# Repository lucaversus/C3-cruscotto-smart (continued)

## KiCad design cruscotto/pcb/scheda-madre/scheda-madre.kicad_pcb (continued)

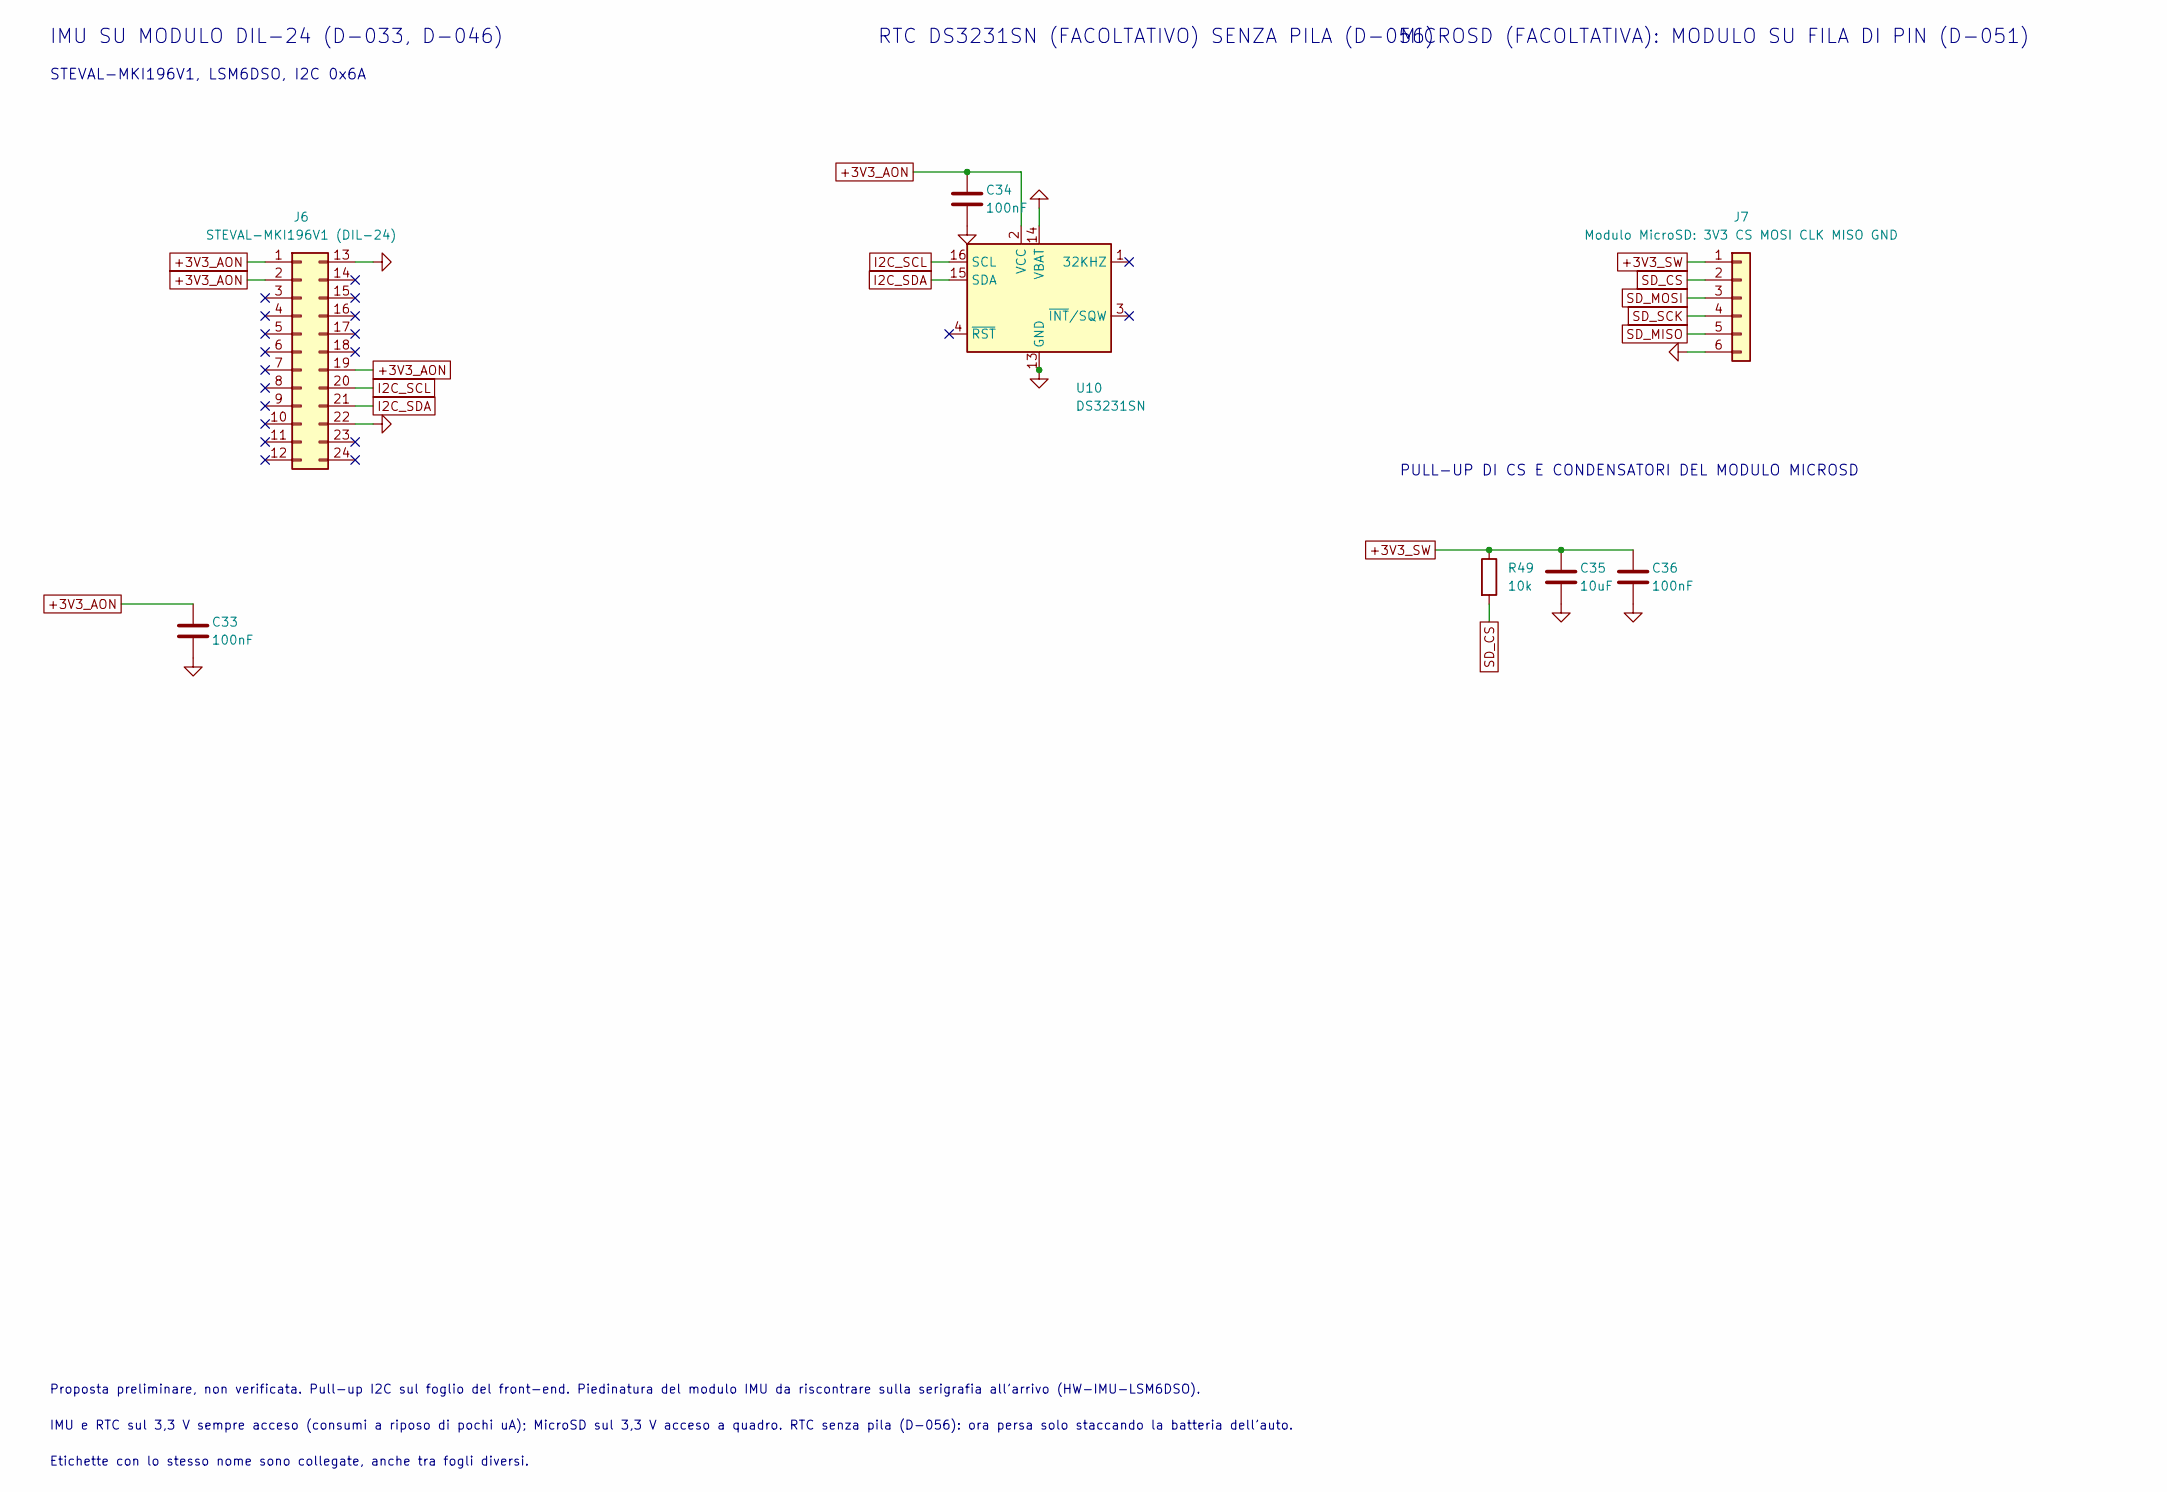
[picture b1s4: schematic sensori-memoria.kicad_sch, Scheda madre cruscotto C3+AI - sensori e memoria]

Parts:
C33, C34, C36: 100nF; C_0805_2012Metric_Pad1.18x1.45mm_HandSolder
C35: 10uF; C_1206_3216Metric_Pad1.33x1.80mm_HandSolder
J6: STEVAL-MKI196V1 (DIL-24); ST_DIL24_Adapter_W15.0mm
J7: Modulo MicroSD: 3V3 CS MOSI CLK MISO GND; PinHeader_1x06_P2.54mm_Vertical
R49: 10k; R_0805_2012Metric_Pad1.20x1.40mm_HandSolder
U10: DS3231SN; SOIC-16W_7.5x10.3mm_P1.27mm

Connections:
+3V3_AON: C33.1, C34.1, J6.1, J6.2, J6.19, U10.2 (VCC); also elsewhere on the board
+3V3_SW: C35.1, C36.1, J7.1, R49.1; also elsewhere on the board
GND: C33.2, C34.2, C35.2, C36.2, J6.13, J6.22, J7.6, U10.5 (GND), U10.6 (GND), U10.7 (GND), U10.8 (GND), U10.9 (GND), U10.10 (GND), U10.11 (GND), U10.12 (GND), U10.13 (GND), U10.14 (VBAT); also elsewhere on the board
I2C_SCL: J6.20, U10.16 (SCL); also elsewhere on the board
I2C_SDA: J6.21, U10.15 (SDA); also elsewhere on the board
SD_CS: J7.2, R49.2; also elsewhere on the board
SD_MISO: J7.5; also elsewhere on the board
SD_MOSI: J7.3; also elsewhere on the board
SD_SCK: J7.4; also elsewhere on the board

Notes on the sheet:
IMU SU MODULO DIL-24 (D-033, D-046)
STEVAL-MKI196V1, LSM6DSO, I2C 0x6A
RTC DS3231SN (FACOLTATIVO) SENZA PILA (D-056)
MICROSD (FACOLTATIVA): MODULO SU FILA DI PIN (D-051)
PULL-UP DI CS E CONDENSATORI DEL MODULO MICROSD
Proposta preliminare, non verificata. Pull-up I2C sul foglio del front-end. Piedinatura del modulo IMU da riscontrare sulla serigrafia all’arrivo (HW-IMU-LSM6DSO).
IMU e RTC sul 3,3 V sempre acceso (consumi a riposo di pochi uA); MicroSD sul 3,3 V acceso a quadro. RTC senza pila (D-056): ora persa solo staccando la batteria dell’auto.
Etichette con lo stesso nome sono collegate, anche tra fogli diversi.

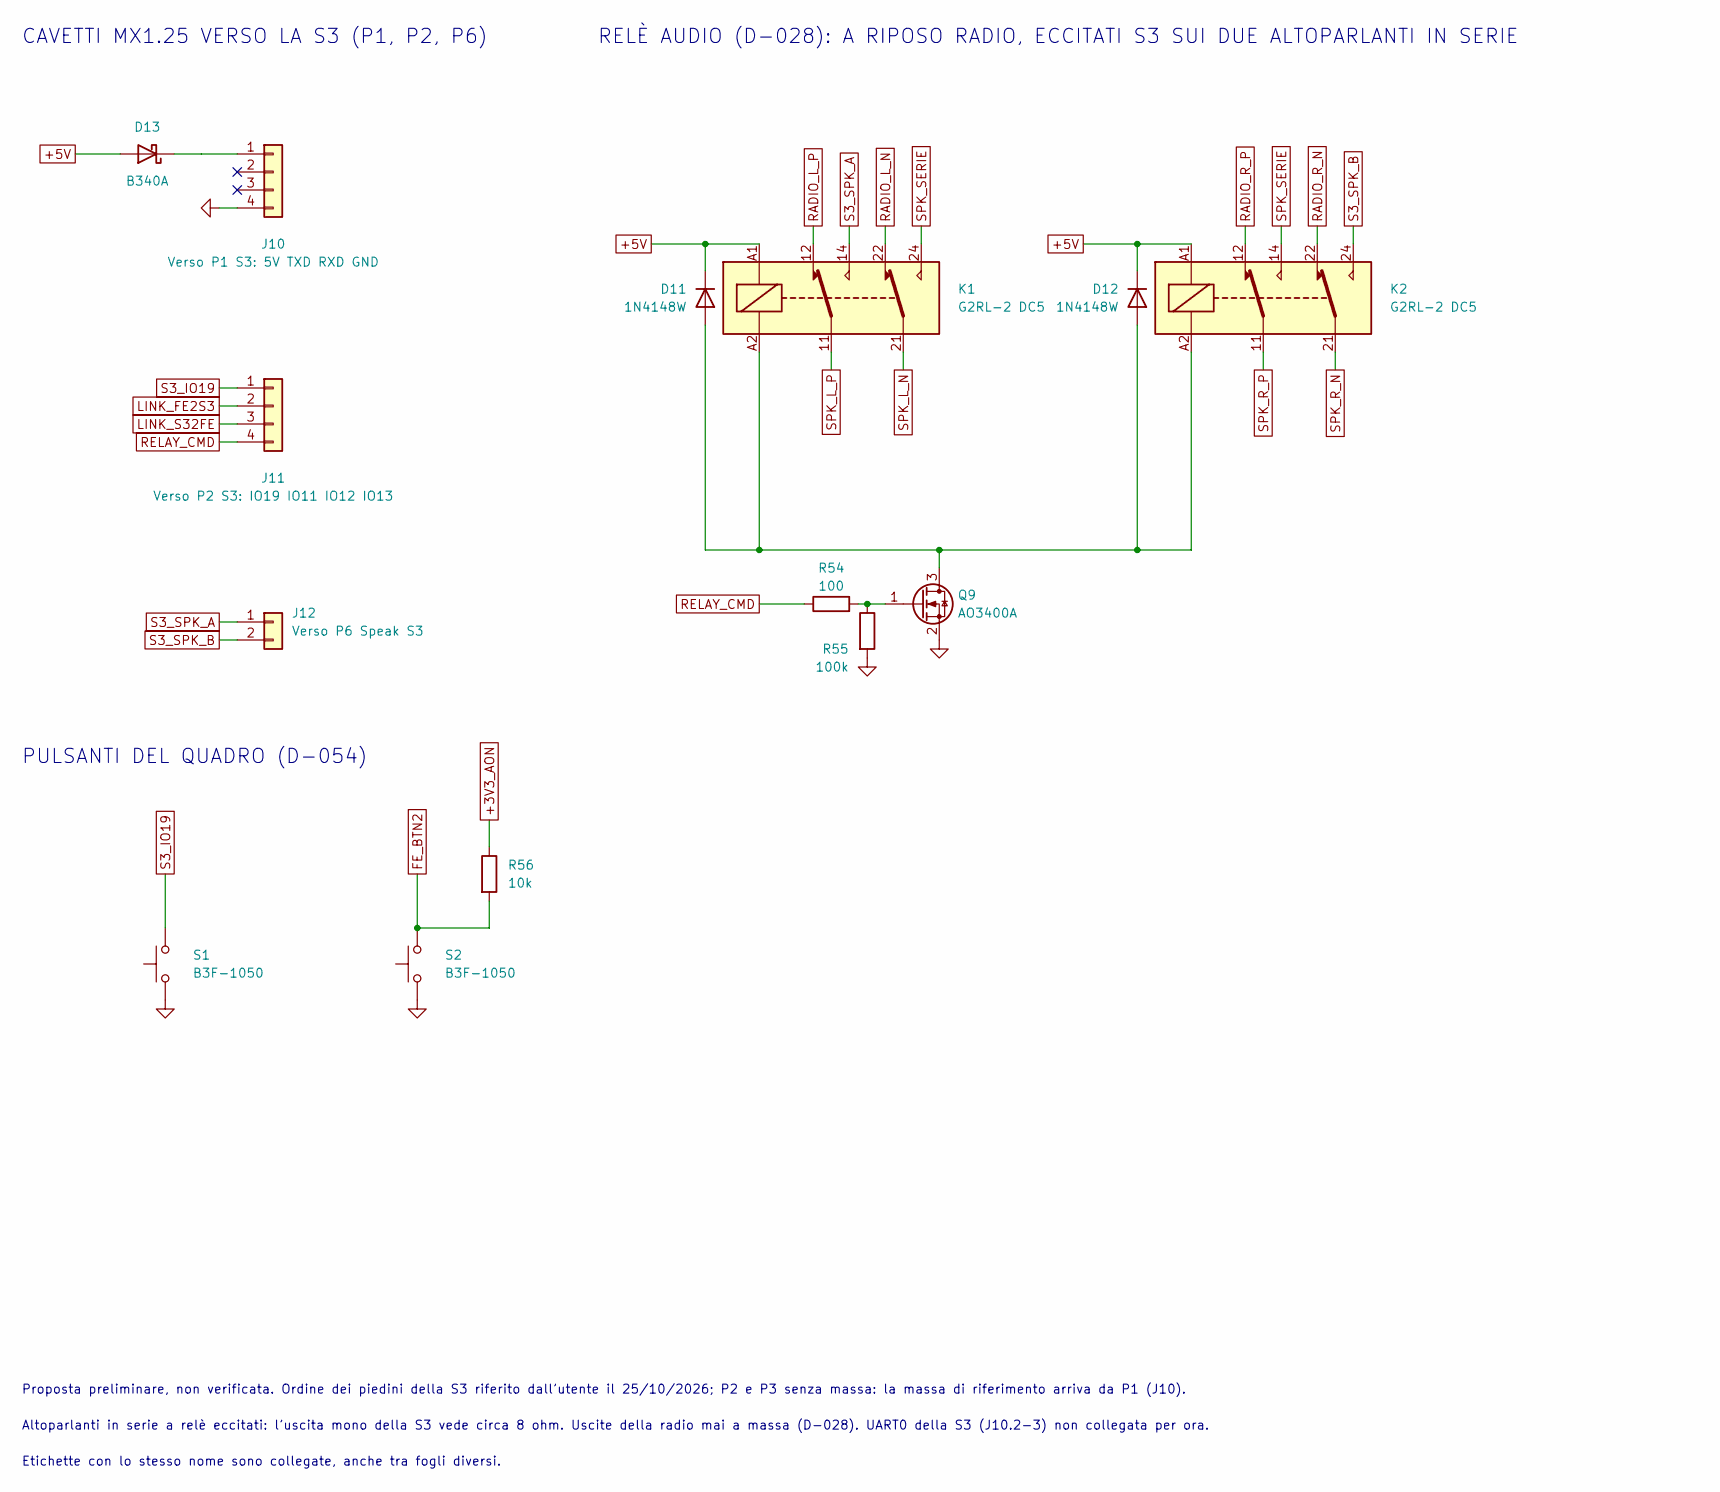
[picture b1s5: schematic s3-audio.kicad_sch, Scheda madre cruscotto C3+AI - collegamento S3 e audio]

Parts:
D11, D12: 1N4148W; D_SOD-123
D13: B340A; D_SMA
J10: Verso P1 S3: 5V TXD RXD GND; SolderWire-0.127sqmm_1x04_P3.7mm_D0.48mm_OD1mm
J11: Verso P2 S3: IO19 IO11 IO12 IO13; SolderWire-0.127sqmm_1x04_P3.7mm_D0.48mm_OD1mm
J12: Verso P6 Speak S3; SolderWire-0.127sqmm_1x02_P3.7mm_D0.48mm_OD1mm
K1, K2: G2RL-2 DC5; Relay_DPDT_Omron_G2RL-2
Q9: AO3400A; SOT-23
R54: 100; R_0805_2012Metric_Pad1.20x1.40mm_HandSolder
R55: 100k; R_0805_2012Metric_Pad1.20x1.40mm_HandSolder
R56: 10k; R_0805_2012Metric_Pad1.20x1.40mm_HandSolder
S1, S2: B3F-1050; SW_PUSH_6mm_H7.3mm

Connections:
+3V3_AON: R56.1; also elsewhere on the board
+5V: D11.1 (K), D12.1 (K), D13.2 (A), K1.A1, K2.A1; also elsewhere on the board
FE_BTN2: R56.2, S2.2; also elsewhere on the board
GND: J10.4, Q9.2 (S), R55.2, S1.1, S2.1; also elsewhere on the board
LINK_FE2S3: J11.2; also elsewhere on the board
LINK_S32FE: J11.3; also elsewhere on the board
unnamed: D11.2 (A), D12.2 (A), K1.A2, K2.A2, Q9.3 (D)
unnamed: D13.1 (K), J10.1
unnamed: Q9.1 (G), R54.2, R55.1
RADIO_L_N: K1.22; also elsewhere on the board
RADIO_L_P: K1.12; also elsewhere on the board
RADIO_R_N: K2.22; also elsewhere on the board
RADIO_R_P: K2.12; also elsewhere on the board
RELAY_CMD: J11.4, R54.1
S3_IO19: J11.1, S1.2
S3_SPK_A: J12.1, K1.14
S3_SPK_B: J12.2, K2.24
SPK_L_N: K1.21; also elsewhere on the board
SPK_L_P: K1.11; also elsewhere on the board
SPK_R_N: K2.21; also elsewhere on the board
SPK_R_P: K2.11; also elsewhere on the board
SPK_SERIE: K1.24, K2.14

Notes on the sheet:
PULSANTI DEL QUADRO (D-054)
CAVETTI MX1.25 VERSO LA S3 (P1, P2, P6)
RELÈ AUDIO (D-028): A RIPOSO RADIO, ECCITATI S3 SUI DUE ALTOPARLANTI IN SERIE
Proposta preliminare, non verificata. Ordine dei piedini della S3 riferito dall’utente il 25/10/2026; P2 e P3 senza massa: la massa di riferimento arriva da P1 (J10).
Altoparlanti in serie a relè eccitati: l’uscita mono della S3 vede circa 8 ohm. Uscite della radio mai a massa (D-028). UART0 della S3 (J10.2-3) non collegata per ora.
Etichette con lo stesso nome sono collegate, anche tra fogli diversi.

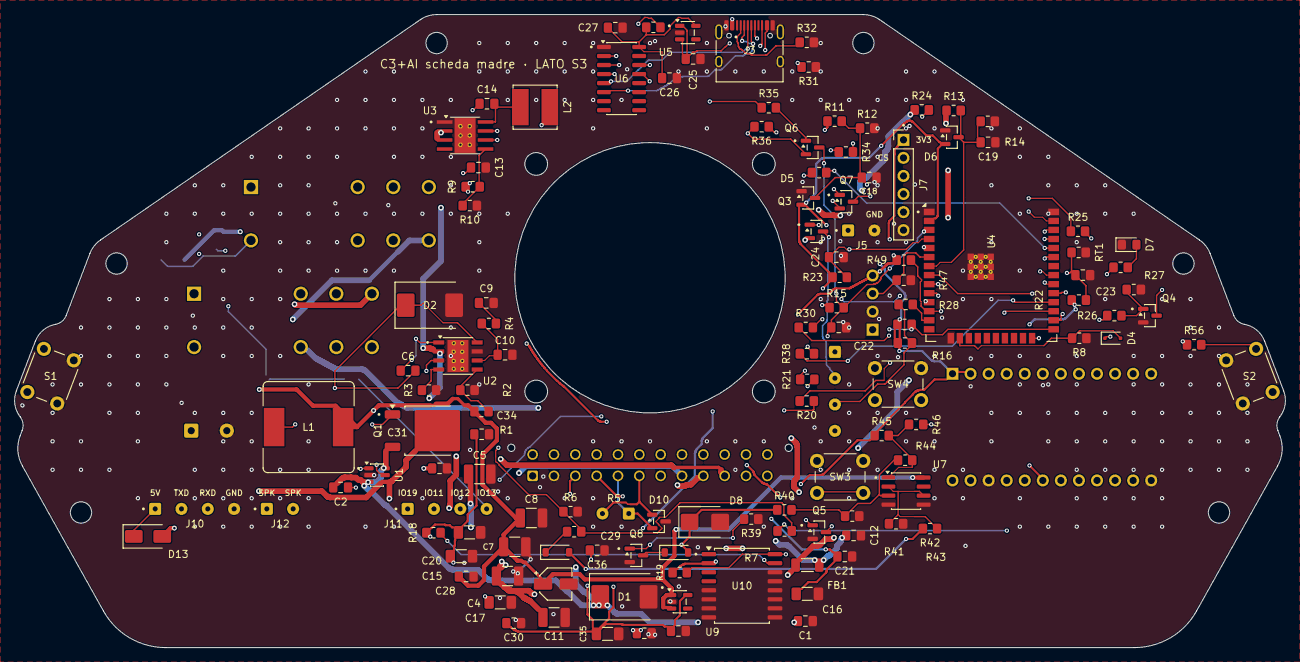
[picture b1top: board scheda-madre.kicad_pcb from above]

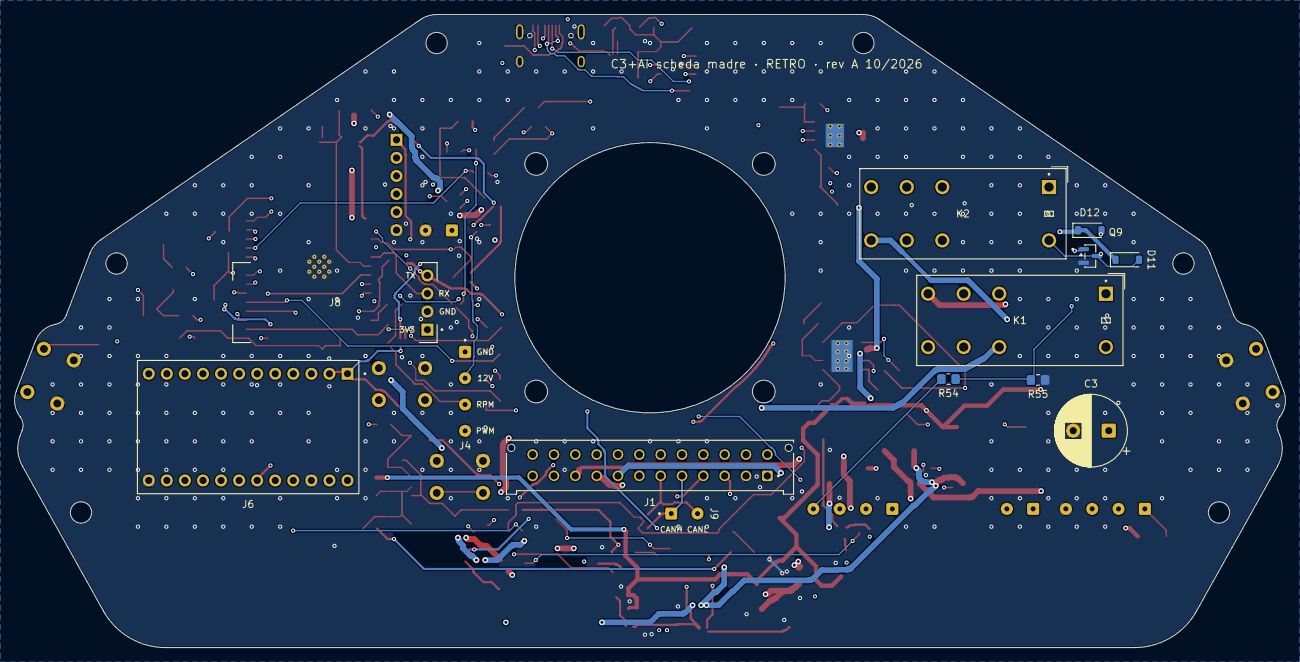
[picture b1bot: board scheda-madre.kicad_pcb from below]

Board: 4 copper layers, 178.7 x 89.0 mm, 149 parts (14 on the bottom side), 95 nets.

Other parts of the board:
H1, H2, H3, H4, H5, H6: Foro Ø3 (D-045); MountingHole_3mm
H7, H8, H9, H10: Ventola 40x40; MountingHole_3.2mm_M3
VENT1: Delta AFB0412VA-00

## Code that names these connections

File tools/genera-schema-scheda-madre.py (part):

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       note='Vie 16-24 riserva; assegnazione bozza (D-044)')
wire((30.48, 160.02), (30.48, 165.1))
flag('VBAT_IN', (30.48, 160.02))
label('VBAT_IN', (30.48, 165.1), 270)
flag('GND', (45.72, 160.02))
gnd((45.72, 160.02))

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wire((78.74, Y), 'D1.1', 'C1.1', (97.79, Y), (114.3, Y), 'Q1.3')
wire('Q1.2', (129.54, Y), (134.62, Y), 'C3.1', (149.86, Y), 'FB1.1')
wire('FB1.2', (165.1, Y), (170.18, Y))
label('VBAT_IN', (78.74, Y), 180)
wire((134.62, Y), (134.62, Y - 5.08))
label('VBAT_P', (134.62, Y - 5.08), 90)
flag('VBAT_P', (149.86, Y))
flag('+12V_F', (165.1, Y))
label('+12V_F', (170.18, Y), 0)
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wire('D3.1', 'R5.1')
wire('R5.2', (238.76, 88.9))
wire('D3.2', (209.55, 88.9))
label('KEY_IN', (209.55, 88.9), 180)
R('R7', '10k', 228.6, 101.6, 'HOLD_D', 'EN_5V', rot=90)
symbol('D4', 'Device:D_Schottky', 'BAT54J', 'Diode_SMD:D_SOD-323F', 215.9, 101.6, rot=180,
       nets={'1': 'HOLD_D', '2': 'PWR_HOLD'})
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wire('R7.2', (238.76, 101.6))
R('R6', '84.5k', 238.76, 105.41, 'EN_5V', 'GND')
gnd('R6.2', 0)
R('R8', '100k', 205.74, 105.41, 'PWR_HOLD', 'GND', note='A riposo spento (GPIO13 flottante al reset)')
gnd('R8.2', 0)
wire('D4.2', 'R8.1', (200.66, 101.6))
label('PWR_HOLD', (200.66, 101.6), 180)
# Bootstrap, commutazione, diodo, induttanza e uscita.
C('C6', '100nF', 271.78, 54.61, 'U2_BOOT', 'SW_5V')
wire('U2.1', (266.7, 58.42), (266.7, 48.26), (271.78, 48.26), 'C6.1')
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text(71.12, 30.48, 'INGRESSO 12 V E PROTEZIONI (D-030)')
text(195.58, 27.94, 'DOMINIO PRINCIPALE 5 V 3,5 A: S3, AUDIO (accensione: chiave O mantenimento)')
text(195.58, 142.24, 'DOMINIO SEMPRE ACCESO 3,3 V 1 A: FRONT-END, SENSORI (D-031)')
text(71.12, 198.12, 'MISURE PER IL FRONT-END: KEY_SENSE -> GPIO39, VBAT_SENSE -> GPIO35, PWR_HOLD <- GPIO13')
text(25.4, 236.22, 'Proposta preliminare, non verificata. Fusibile di ramo nel cablaggio (HW-FUSE-HOLDER). '
                   'Montaggio a mano (D-046): U2/U3 con piazzola esposta, saldatura dal retro attraverso i fori termici.', 1.27)
text(25.4, 241.3, 'Consumo a riposo stimato: U1 80 uA + U3 26 uA + partitori ~25 uA + front-end in sonno: < 1 mA (D-030), '
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R('R35', '10k', 134.62, 91.44, 'CH_DTR', 'Q6_B', rot=90)
wire('R35.2', 'Q6.1')
wire('R35.1', (128.27, 91.44))
label('CH_DTR', (128.27, 91.44), 180)
symbol('Q7', NPN, 'MMBT3904', SOT23, 147.32, 127, nets={'1': 'Q7_B', '2': 'CH_DTR', '3': 'FE_IO0'},
       txt=((-5.08, -5.08), (-5.08, -2.54), 'right'))
tag('Q7.3')
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R('R36', '10k', 134.62, 127, 'CH_RTS', 'Q7_B', rot=90)
wire('R36.2', 'Q7.1')
wire('R36.1', (128.27, 127))
label('CH_RTS', (128.27, 127), 180)

# --- Programmazione a banco: USB-C + CH340C alimentato solo dalla USB (nessun consumo in auto) ---
symbol('J3', 'Connector:USB_C_Receptacle_USB2.0_16P', 'USB-C (solo a banco)',
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wire('U6.2', 'R33.1')
wire('U6.3', 'R34.1')
wire('R33.2', (120.65, 55.88))
label('FE_U0RXD', (120.65, 55.88), 0)
wire('R34.2', (120.65, 58.42))
label('FE_U0TXD', (120.65, 58.42), 0)
tag('U6.13')
tag('U6.14')

# --- Avvio, LED, I2C, collegamento con l'S3 -------------------------------------------
X0 = 256.54
label('FE_IO0', (X0, 60.96), 180)
R('R16', '10k', X0 + 7.62, 57.15, '+3V3_AON', 'FE_IO0')
symbol('SW4', 'Switch:SW_Push', 'BOOT', 'Button_Switch_THT:SW_PUSH_6mm', X0 + 15.24, 66.04, rot=90,
       nets={'1': 'GND', '2': 'FE_IO0'}, txt=((0, 10.16), (0, 12.7), ''))
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wire((X0, 60.96), 'R16.2', 'SW4.2')
wire('R16.1', (X0 + 7.62, 50.8))
label('+3V3_AON', (X0 + 7.62, 50.8), 90)
label('FE_LED', (X0, 81.28), 180)
R('R17', '1k', X0 + 10.16, 81.28, 'FE_LED', 'LED_A', rot=90)
symbol('D7', 'Device:LED', 'verde', 'LED_SMD:LED_0805_2012Metric_Pad1.15x1.40mm_HandSolder', X0 + 25.4, 81.28,
       rot=180, nets={'1': 'GND', '2': 'LED_A'})
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for r in ('R18', 'R19'):
    tag(f'{r}.2')
# Collegamento seriale con l'S3 (fe_link): 1k in serie limitano la corrente verso l'S3 spenta.
label('FE_TX', (X0, 121.92), 180)
R('R20', '1k', X0 + 10.16, 121.92, 'FE_TX', 'LINK_FE2S3', rot=90)
wire((X0, 121.92), 'R20.1')
wire('R20.2', (X0 + 20.32, 121.92))
label('LINK_FE2S3', (X0 + 20.32, 121.92), 0)
label('FE_RX', (X0, 132.08), 180)
R('R21', '1k', X0 + 10.16, 132.08, 'FE_RX', 'LINK_S32FE', rot=90)
wire((X0, 132.08), 'R21.1')
wire('R21.2', (X0 + 20.32, 132.08))
label('LINK_S32FE', (X0 + 20.32, 132.08), 0)

# --- Temperature: NTC 100k sulla scheda (GPIO32) e vicino al display (GPIO36), 16 uA ciascuna ---
R('R22', '100k', X0 + 5.08, 151.13, '+3V3_AON', 'NTC_PCB')
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gnd('RT1.2', 0)
shunt('C23', '100nF', X0 + 12.7, 154.94, 'NTC_PCB')
wire('R22.2', 'C23.1', (X0 + 20.32, 154.94))
label('NTC_PCB', (X0 + 20.32, 154.94), 0)
R('R23', '100k', X0 + 63.5, 151.13, '+3V3_AON', 'NTC_DISP')
wire('R23.1', (X0 + 63.5, 144.78))
label('+3V3_AON', (X0 + 63.5, 144.78), 90)
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wire('J5.2', (X0 + 78.74, 157.48))
gnd((X0 + 78.74, 157.48))
wire('R23.2', (X0 + 55.88, 154.94))
label('NTC_DISP', (X0 + 55.88, 154.94), 180)

# --- Ventola 12 V (D-031): alimentazione staccata da Q3 a riposo, velocità PWM, giri ---------
label('+12V_F', (X0, 185.42), 180)
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R('R27', '100k', X0 + 10.16, 209.55, 'Q4_B', 'GND', note='Tiene la ventola spenta al reset (e GPIO2 basso)')
gnd('R27.2', 0)
wire((X0 - 5.08, 205.74), 'R26.1')
label('FAN_EN', (X0 - 5.08, 205.74), 180)
wire('R26.2', 'R27.1', 'Q4.1')
symbol('J4', 'Connector_Generic:Conn_01x04', 'Ventola Delta AFB0412VA-00 (D-052)', WIRE % 4,
       X0 + 68.58, 187.96, nets={'1': 'GND', '2': '+12V_FAN', '3': 'FAN_SENSE', '4': 'FAN_CTRL'},
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for n in ('1', '3', '4'):
    tag(f'J4.{n}')
# Giri: uscita a collettore aperto della ventola, pull-up a 3,3 V e 1k in serie verso GPIO14.
label('FAN_SENSE', (X0 + 81.28, 210.82), 180)
R('R28', '10k', X0 + 88.9, 207.01, '+3V3_AON', 'FAN_SENSE')
R('R29', '1k', X0 + 99.06, 210.82, 'FAN_SENSE', 'FAN_TACH', rot=90)
wire((X0 + 81.28, 210.82), 'R28.2', 'R29.1')
wire('R28.1', (X0 + 88.9, 200.66))
label('+3V3_AON', (X0 + 88.9, 200.66), 90)
wire('R29.2', (X0 + 109.22, 210.82))
label('FAN_TACH', (X0 + 109.22, 210.82), 0)
# Velocità: ingresso PWM della ventola a 4 fili pilotato a collettore aperto (logica invertita).
symbol('Q5', NPN, 'MMBT3904', SOT23, X0 + 91.44, 236.22, nets={'1': 'Q5_B', '2': 'GND', '3': 'FAN_CTRL'},
       txt=((5.08, -1.27), (5.08, 1.27), 'left'))
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R('R30', '1k', X0 + 78.74, 236.22, 'FAN_PWM', 'Q5_B', rot=90)
wire('R30.2', 'Q5.1')
wire((X0 + 68.58, 236.22), 'R30.1')
label('FAN_PWM', (X0 + 68.58, 236.22), 180)

text(25.4, 27.94, 'PROGRAMMAZIONE A BANCO: USB-C + CH340C, alimentati solo dalla USB')
text(124.46, 76.2, 'RESET AUTOMATICO (DTR/RTS)', 1.5)
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
# --- K-line: circuito KL-001 rev F (data-logger/docs/kline-autocostruita.md) con protezioni ---
YK = 50.8
label('KLINE', (30.48, YK), 180)
symbol('D8', 'Device:D_TVS', 'SMBJ26CA', 'Diode_SMD:D_SMB', 40.64, YK + 3.81, rot=270,
       nets={'1': 'KLINE', '2': 'GND'}, note='Aggiunta per l\'auto: transitori sulla linea K')
gnd('D8.2', 0)
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gnd('R39.2', 0)
wire('R38.2', 'R39.1', 'Q8.1')
wire((30.48, 67.31), 'R38.1')
label('KL_TX', (30.48, 67.31), 180)
R('R40', '68k', 81.28, 54.61, 'KLINE', 'KL_VSENSE')
R('R41', '10k', 81.28, 62.23, 'KL_VSENSE', 'GND')
gnd('R41.2', 0)
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symbol('U7', 'Comparator:LM2903', 'LM2903B', SOIC8, 101.6, 60.96, unit=1,
       nets={'1': 'KL_RAW', '2': 'KL_VREF', '3': 'KL_VSENSE'}, txt=((0, 7.62), (0, 10.16), ''))
wire('R40.2', (88.9, 58.42), 'U7.3')
R('R42', '150k', 83.82, 76.2, 'KEY_IN', 'KL_VREF', rot=90,
  note='Soglia riferita alla linea chiave invece che alla batteria: nessun consumo a riposo')
R('R43', '10k', 91.44, 80.01, 'KL_VREF', 'GND')
gnd('R43.2', 0)
wire('U7.2', (91.44, 63.5), 'R43.1')
wire('R42.2', (91.44, 76.2), (96.52, 76.2))
label('KL_VREF', (96.52, 76.2), 0)
wire('R42.1', (76.2, 76.2))
label('KEY_IN', (76.2, 76.2), 180)
R('R44', '330k', 101.6, 48.26, 'KL_VSENSE', 'KL_RAW', rot=90, note='Isteresi (D-022)')
wire((88.9, 58.42), (88.9, 48.26), 'R44.1')
wire('R44.2', (114.3, 48.26), (114.3, 60.96), 'U7.1')
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R('R46', '1k', 132.08, 60.96, 'KL_RAW', 'KL_RX', rot=90)
wire((114.3, 60.96), 'R45.2', 'R46.1')
wire('R46.2', (142.24, 60.96))
label('KL_RX', (142.24, 60.96), 0)
# Seconda metà del comparatore non usata (come rev F) e alimentazione dal 5 V principale.
symbol('U7', 'Comparator:LM2903', 'LM2903B', SOIC8, 101.6, 91.44, unit=2,
       nets={'5': 'GND', '6': 'KL_VREF', '7': None}, txt=((0, 7.62), (0, 10.16), ''))
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  note='GPIO34 non ha resistenze interne: livello definito con il modulo spento')
gnd('R47.2', 0)
wire('J8.3', 'R47.1', (200.66, 68.58))
label('VAN_RX', (200.66, 68.58), 180)
symbol('J9', 'Connector_Generic:Conn_01x02', 'Modulo VAN: CANH CANL', WIRE % 2, 309.88, 66.04,
       nets={'1': 'VAN_DATA', '2': 'VAN_DATAB'}, note='Due fili dal morsetto a vite del modulo (D-060)')
symbol('D10', 'Power_Protection:NUP2105L', 'NUP2105L', SOT23, 284.48, 67.31, rot=90,
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tag('D10.3')
wire((269.24, 64.77), (274.32, 64.77), 'D10.2')
wire((274.32, 64.77), (274.32, 58.42), (302.26, 58.42), (302.26, 66.04), 'J9.1')
label('VAN_DATA', (269.24, 64.77), 180)
wire((269.24, 69.85), (276.86, 69.85), 'D10.1')
wire((276.86, 69.85), (276.86, 76.2), (299.72, 76.2), (299.72, 68.58), 'J9.2')
label('VAN_DATAB', (269.24, 69.85), 180)
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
